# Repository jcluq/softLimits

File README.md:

# Elipses

Elipses are a series of kinetic sculptures which base their design on a string loop throwing contraption referred to as a string shooter. The mechanism consists of two motors rotating in opposite directions, which impulse a loop of yarn to a distance dependent on the speed of the motors and the length of the string. Because the string is looped, the yarn returns to the string shooter, getting fed again into the motors. This continuous throw generates a levitating elliptical shape. This phenomenon is quite interesting and eye-catching, as it produces a peculiar behavior that our perception is not used to experiencing.

## softLimits

On softLimits, 5 different nodes are located in the space close to eachother. Each node consists of a string shooter mounted on a servo motor to control the angle of throw. The servo motor is then mounted on top of a rotating platform controlled by a stepper motor. A slip ring is used to connect the servo motor and allow 360+ degrees of rotation without entangling the cables. All the motors are driven by a ESP32 based micro controller which rests on a custom PCB for handling all the copper circuitry.

The esp32 micro controller on each node allows them to do be controlled via Wi-Fi through OSC messages using UDP protocol. A custom software made in Processing acts as an interface for the nodes, allowing real time visualization of position and speed, as well as sending messages to them in order to change their parameters.

For the Soft Limits choreography, each node has a behaviour assigned to it. Behaviors are made up of 4 different parameters: throwing speed, rotation speed, rotation direction, and shooter angle. The nodes are then allowed to run on these parameters freely, until the software detects a collision between them. When this happens, a "swap" between parameters occurs, changing the shapes and movement of both nodes. When the 5 nodes are allowed to run freely and interact, an ever-changing play takes place.

## PoC (Process of Creation)

The creation of this artwork has meant a multidisciplinary research touching a number of different disciplines: wireless communications, mechanical design, digital fabrication, circuit and PCB design, welding, among many others. 

For the first string shooters I was basing myself on a design created by the user scorch on the page [Thingy verse](https://www.thingiverse.com/thing:3647986). This version was almost entirely made of laser cut parts, which even tho they where quick to produce, they were also very difficult to modify mainly because I didnt had the original archives that were used to design the devices. 

My next step was to create my own string shooter. For this I 3D modeled my own parts with the use of TICAD and start 3d printing the parts. This allowed me to test and modify specific parts and functions in a relative cheap and fast way. I changed the 5VDC motors I was using for faster and stronger 5-24V motors. The hardest obstacle I kept on finding was the lack of friction on the wheels which made contact with the yarn. On a [research](https://www.researchgate.net/publication/338578099_String_Shooter's_overall_shape_in_ambient_air) about the overall shapes of string shooters in air, the use of RC cars wheels was reported successful. After implementing these wheels on my design, I achieved a desired stability on my string shooters. 

For the tilt and pan module, I used a mg996r motor attached to a tilt metal bracket. Due to the screw fixtures on the bracket, setting up the string shooter on top of it was very easily done, by using threaded inserts on the 3d printed material. For the pan mechanism, I designed a tower structure to hold the bearings and the slip ring together, while giving enough space for the tilt mechanism to change angle without obstruction. For all this design process, fusion360 was very useful again as it allowed me to design with a modular a approach, having different parts which would then be "assembled" onto the final object. This modular approach proved to be a great constrain to prototyping because of the constant tests and modifications. 

For the electrical and communication design, I wanted to have a single line of power as the only physical input to each node. I used 12V as my main power and later used a LM1085 power regulator to send 5V to both my servomotor and micro controller. The ESP32 drive the 24VDC motors through an IRL540 mosfet, using PWM to change the throwing speed. The esp uses an A4988 driver in order to translate the stepper movements as well as to set up micro stepping. The mg996r motor is driven simply by a PWM output. 

The PCB was designed in KiCad and its shape and design was made to fit on the previous 3D models designed on Fusion360.

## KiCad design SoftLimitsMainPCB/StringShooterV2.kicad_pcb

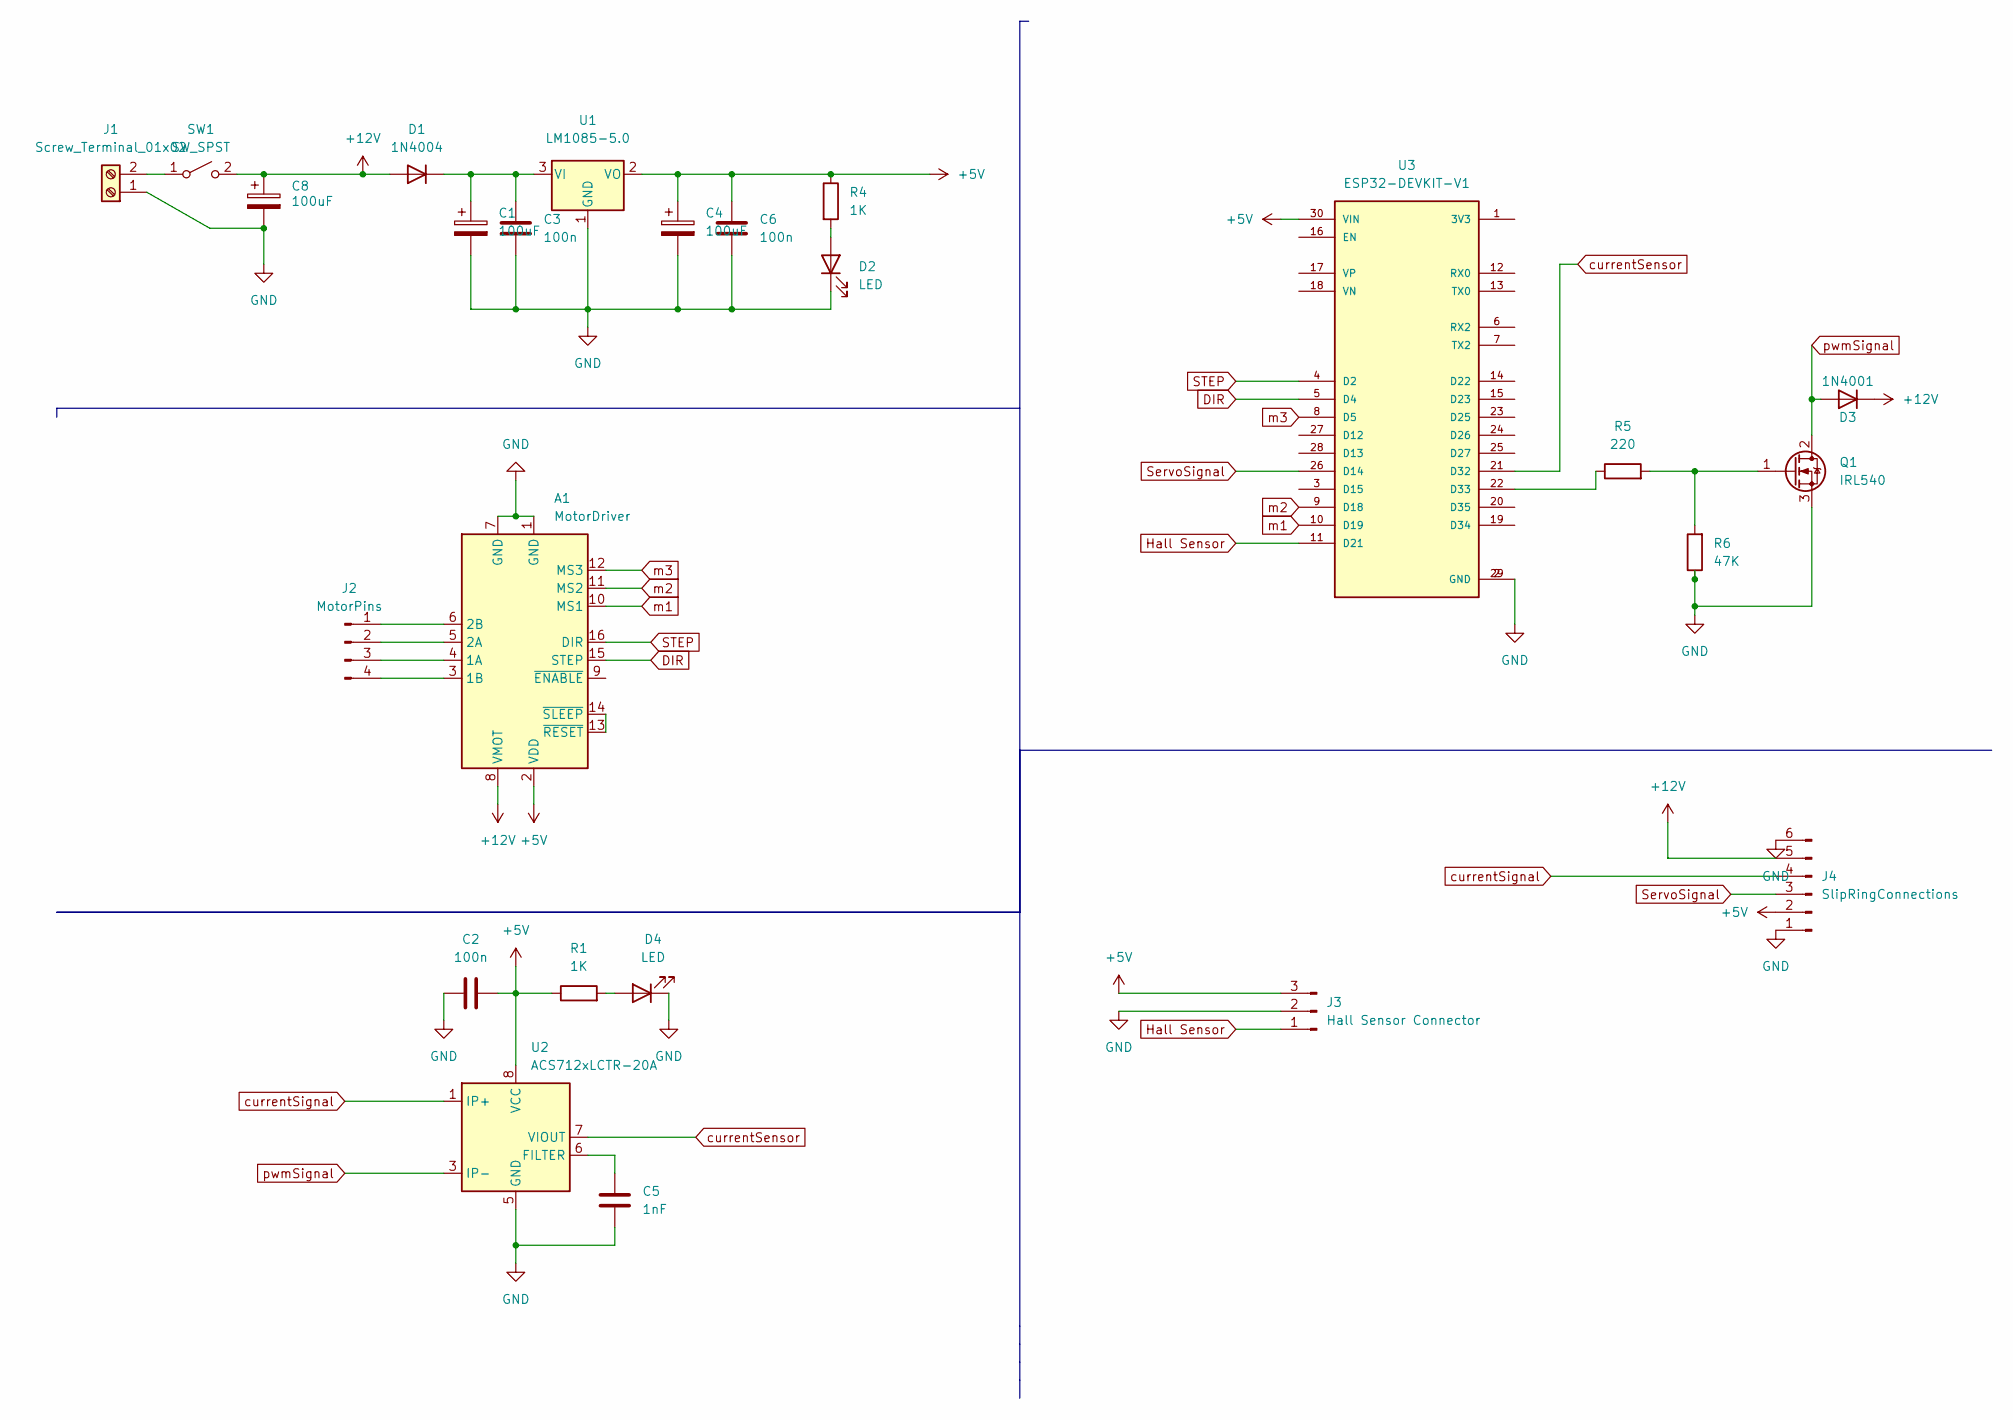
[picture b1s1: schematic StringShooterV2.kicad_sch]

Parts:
A1: MotorDriver; Pololu_Breakout-16_15.2x20.3mm
C1, C4, C8: 100uF; CP_Radial_D6.3mm_P2.50mm
C2, C3, C6: 100n; C_0805_2012Metric_Pad1.18x1.45mm_HandSolder
C5: 1nF; C_0805_2012Metric_Pad1.18x1.45mm_HandSolder
D1: 1N4004; D_SMA_Handsoldering
D2, D4: LED; D_0603_1608Metric_Pad1.05x0.95mm_HandSolder
D3: 1N4001; D_SMA_Handsoldering
J1: Screw_Terminal_01x02; TerminalBlock_bornier-2_P5.08mm
J2: MotorPins; PinSocket_1x04_P2.54mm_Vertical
J3: Hall Sensor Connector; PinSocket_1x03_P2.54mm_Vertical
J4: SlipRingConnections; PinSocket_1x06_P2.54mm_Vertical
Q1: IRL540; TO-220-3_Horizontal_TabDown
R1, R4: 1K; R_0805_2012Metric_Pad1.20x1.40mm_HandSolder
R5: 220; R_0805_2012Metric_Pad1.20x1.40mm_HandSolder
R6: 47K; R_0805_2012Metric_Pad1.20x1.40mm_HandSolder
SW1: SW_SPST; mts102
U1: LM1085-5.0; TO-263-3_TabPin2
U2: ACS712xLCTR-20A; SOIC-8_3.9x4.9mm_P1.27mm
U3: ESP32-DEVKIT-V1; MODULE_ESP32_DEVKIT_V1; PARTREV N/A

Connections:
+5V: A1.2 (VDD), C2.2, C4.1, C6.1, J3.3, J4.2, R1.1, R4.1, U1.2 (VO), U2.8 (VCC), U3.30 (VIN)
+12V: A1.8 (VMOT), C8.1, D1.2 (A), D3.1 (K), J4.5, SW1.2 (B)
DIR: A1.15 (STEP), U3.5 (D4)
GND: A1.1 (GND), A1.7 (GND), C1.2, C2.1, C3.2, C4.2, C5.2, C6.2, C8.2, D2.1 (K), D4.1 (K), J1.1, J3.2, J4.1, J4.6, Q1.3 (S), R6.1, U1.1 (GND), U2.5 (GND), U3.2 (GND), U3.29 (GND)
Hall Sensor: J3.1, U3.11 (D21)
unnamed: A1.3 (1B), J2.4
unnamed: A1.4 (1A), J2.3
unnamed: A1.5 (2A), J2.2
unnamed: A1.6 (2B), J2.1
unnamed: A1.13 (~RESET), A1.14 (~SLEEP)
unnamed: C1.1, C3.1, D1.1 (K), U1.3 (VI)
unnamed: C5.1, U2.6 (FILTER)
unnamed: D2.2 (A), R4.2
unnamed: D4.2 (A), R1.2
unnamed: J1.2, SW1.1 (A)
unnamed: Q1.1 (G), R5.2, R6.2
unnamed: R5.1, U3.22 (D33)
STEP: A1.16 (DIR), U3.4 (D2)
ServoSignal: J4.3, U3.26 (D14)
currentSensor: U2.7 (VIOUT), U3.21 (D32)
currentSignal: J4.4, U2.1 (IP+), U2.2 (IP+)
m1: A1.10 (MS1), U3.10 (D19)
m2: A1.11 (MS2), U3.9 (D18)
m3: A1.12 (MS3), U3.8 (D5)
pwmSignal: D3.2 (A), Q1.2 (D), U2.3 (IP-), U2.4 (IP-)

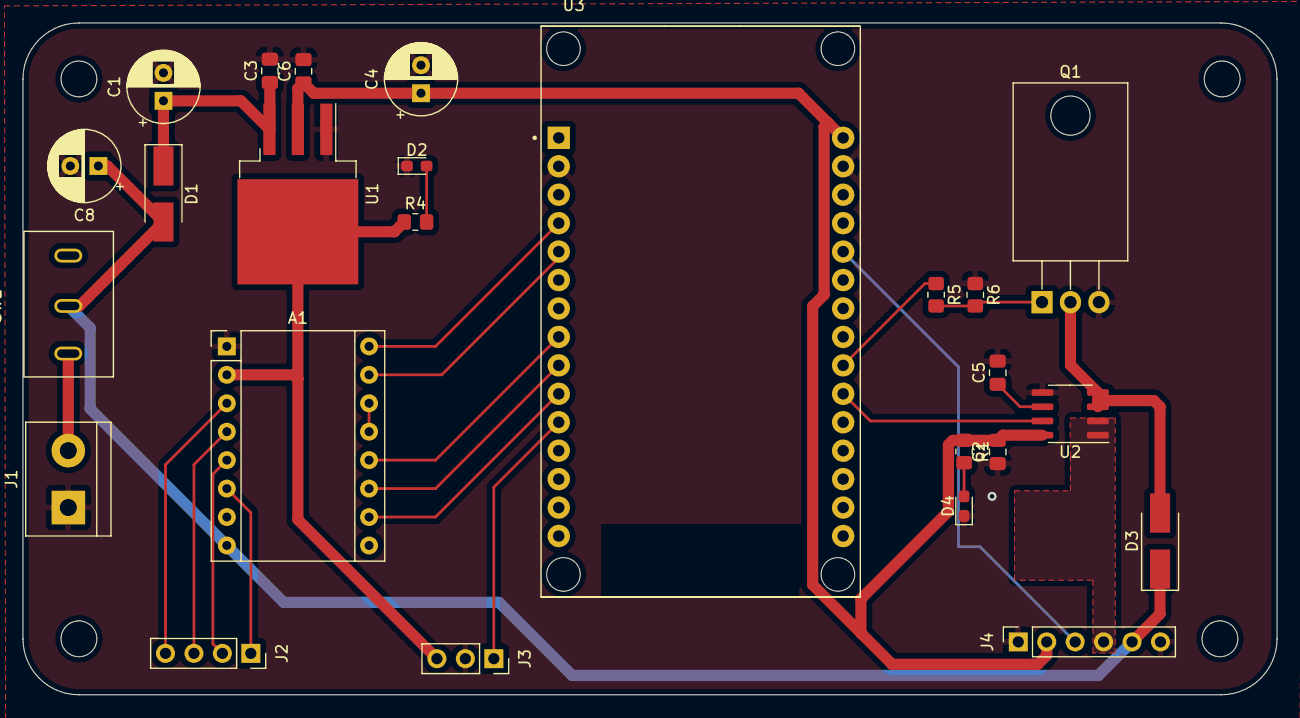
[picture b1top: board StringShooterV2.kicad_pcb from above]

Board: 2 copper layers, 112.0 x 60.0 mm, 25 parts (0 on the bottom side), 25 nets.
